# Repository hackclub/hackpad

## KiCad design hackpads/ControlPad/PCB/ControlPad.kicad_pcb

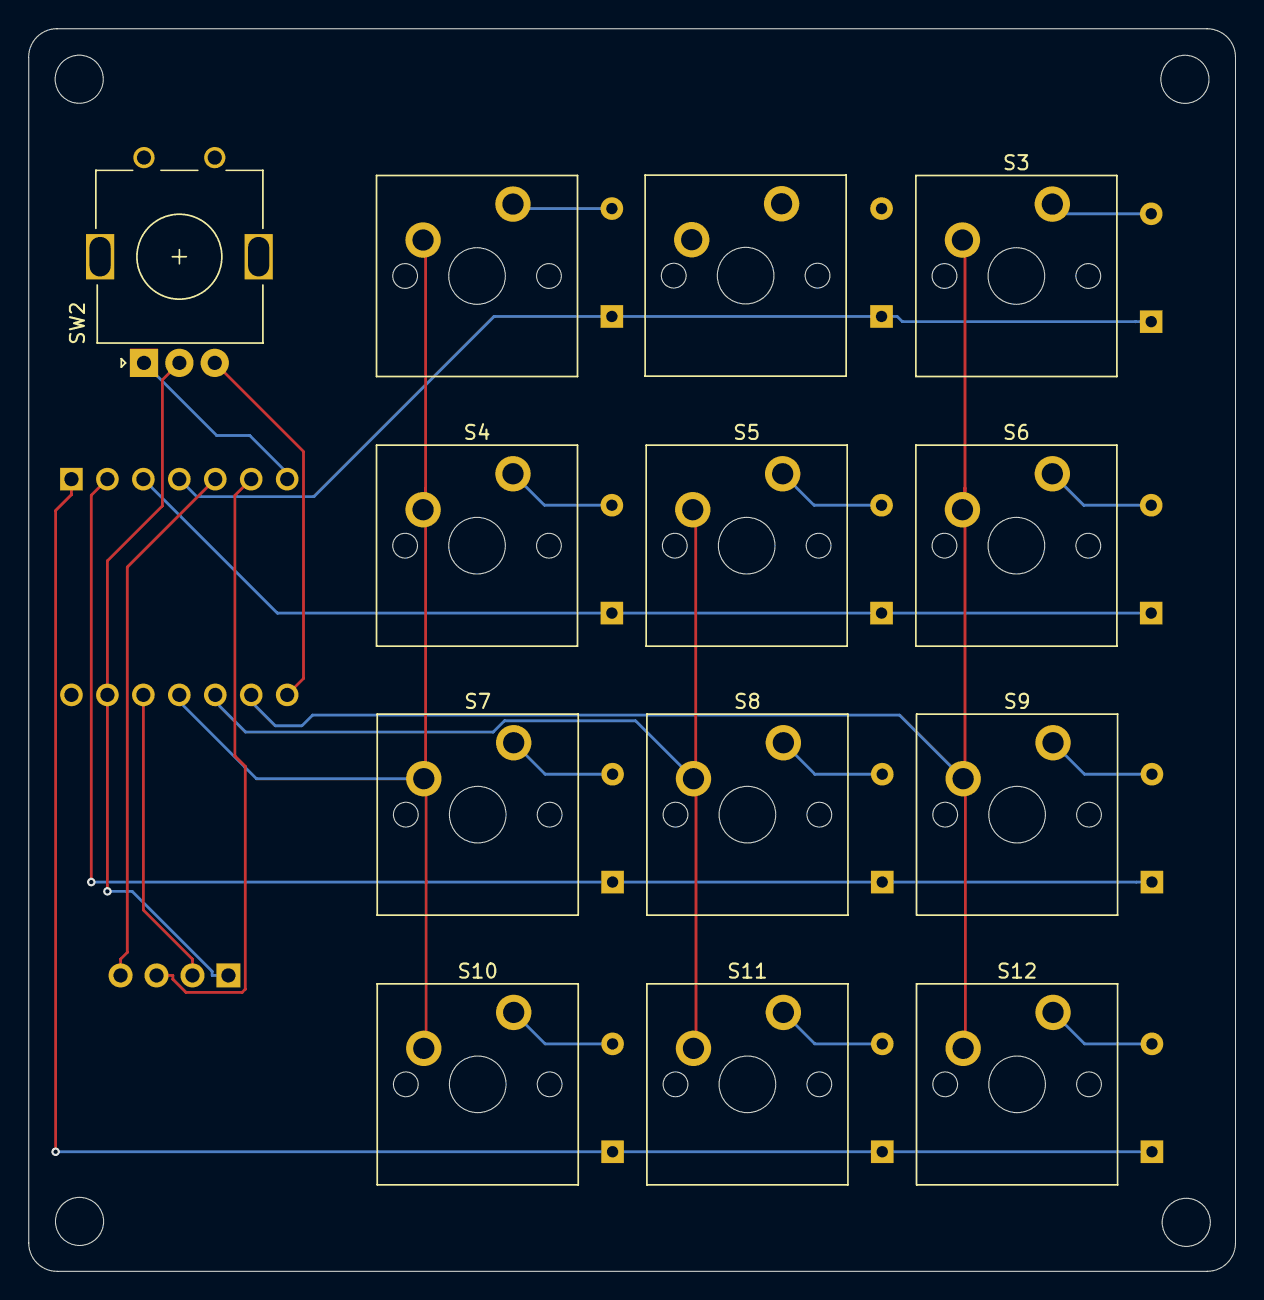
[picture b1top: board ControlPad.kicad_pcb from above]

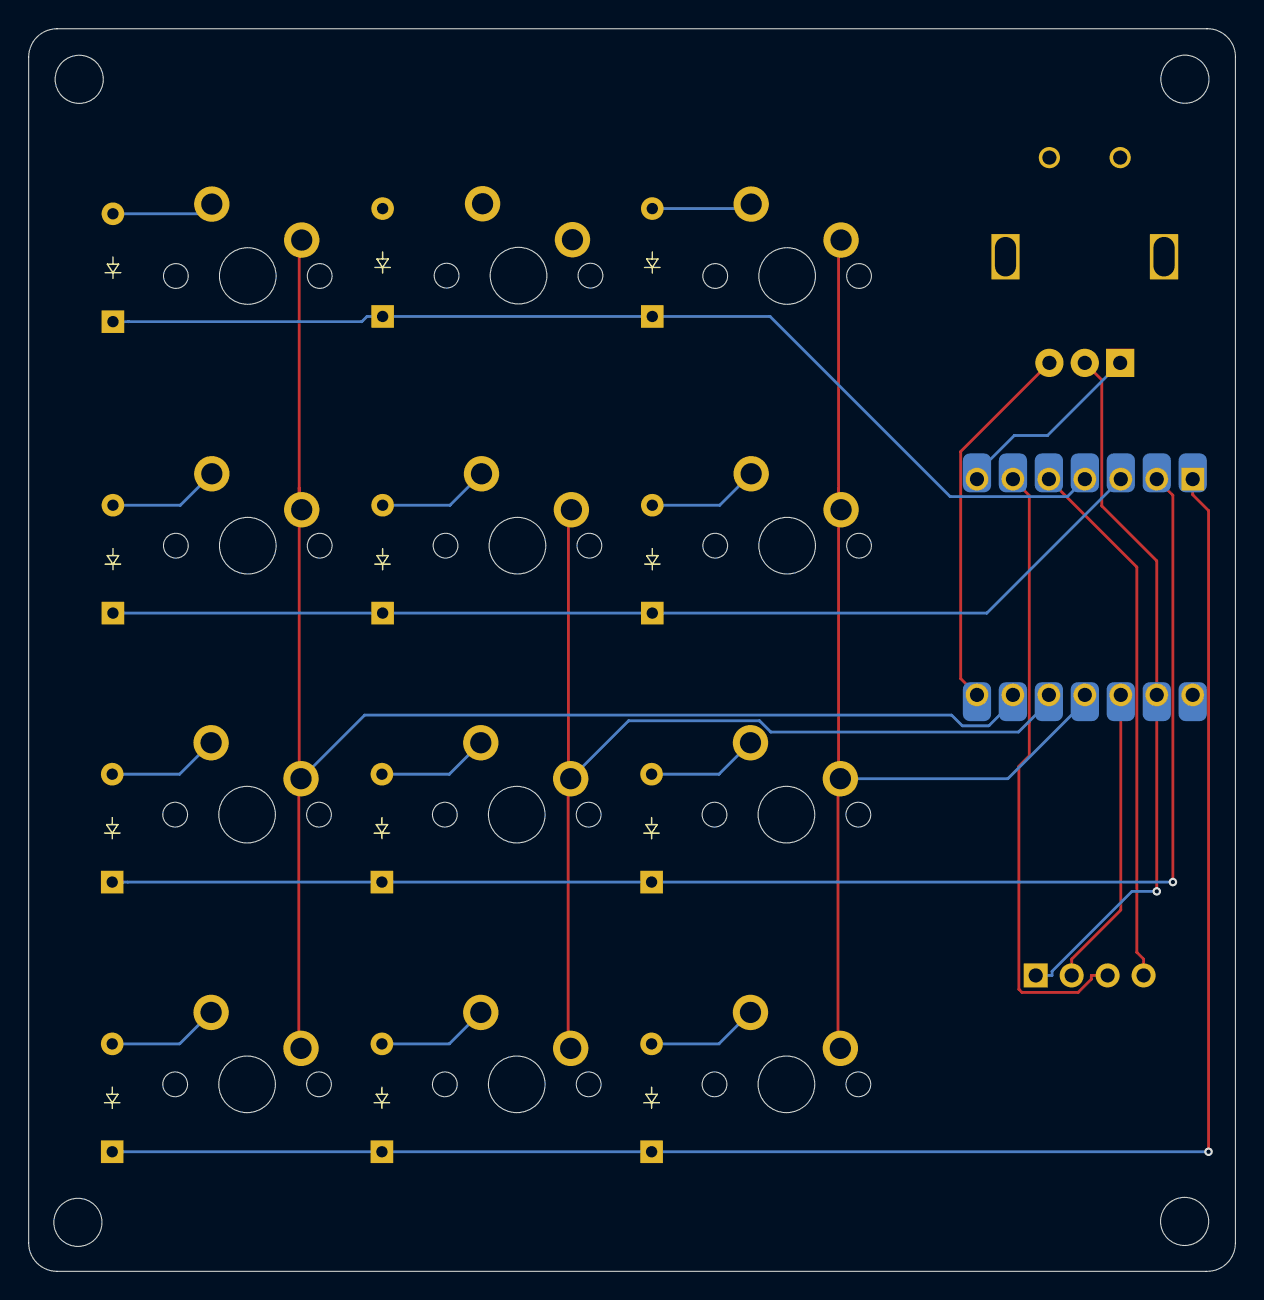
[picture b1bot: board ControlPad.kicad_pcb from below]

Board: 2 copper layers, 85.2 x 87.8 mm, 27 parts (13 on the bottom side), 24 nets.

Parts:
D1, D2, D3, D4, D5, D6, D7, D8, D9, D10, D11, D12: Diode; Diode_DO-35
J2: OLED_128x32
S1, S2, S3, S4, S5, S6, S7, S8, S9, S10, S11, S12: Keyswitch; MX_PCB_1.00u
SW2: RotaryEncoder; RotaryEncoder_Alps_EC11E_Vertical_H20mm
U1: MCU_Seeed_XIAO_RP2040; Seeed_XIAO_RP2040

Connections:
+3.3V: J2.2 (VCC), U1.12 (3V3)
Column 0: S1.1, S4.1, S7.1, S10.1, U1.11 (PA6_A10_D10_MOSI)
Column 1: S5.1, S8.1, S11.1, U1.10 (PA5_A9_D9_MISO)
Column 2: S3.1, S6.1, S9.1, S12.1, U1.9 (PA7_A8_D8_SCK)
GND: J2.1 (GND), SW2.C, U1.13 (GND)
unnamed: D1.2 (A), S1.2
unnamed: D3.2 (A), S3.2
unnamed: D4.2 (A), S4.2
unnamed: D5.2 (A), S5.2
unnamed: D6.2 (A), S6.2
unnamed: D7.2 (A), S7.2
unnamed: D8.2 (A), S8.2
unnamed: D9.2 (A), S9.2
unnamed: D10.2 (A), S10.2
unnamed: D11.2 (A), S11.2
unnamed: D12.2 (A), S12.2
unnamed: J2.3 (SCL), U1.6 (PA9_A5_D5_SCL)
unnamed: J2.4 (SDA), U1.5 (PA8_A4_D4_SDA)
unnamed: SW2.A, U1.7 (PB08_A6_D6_TX)
unnamed: SW2.B, U1.8 (PB09_A7_D7_RX)
Row 0: D1.1 (K), D2.1 (K), D3.1 (K), U1.4 (PA11_A3_D3)
Row 1: D4.1 (K), D5.1 (K), D6.1 (K), U1.3 (PA10_A2_D2)
Row 2: D7.1 (K), D8.1 (K), D9.1 (K), U1.2 (PA4_A1_D1)
Row 3: D10.1 (K), D11.1 (K), D12.1 (K), U1.1 (PA02_A0_D0)

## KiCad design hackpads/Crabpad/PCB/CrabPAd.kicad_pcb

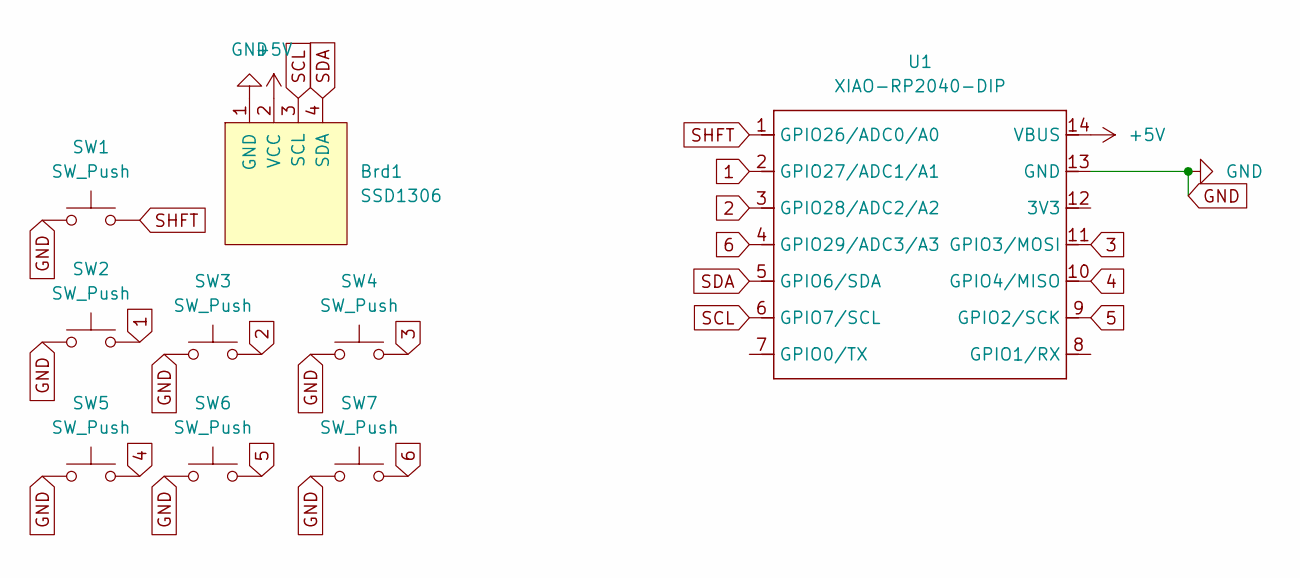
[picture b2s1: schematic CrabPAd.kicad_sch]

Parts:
Brd1: SSD1306; 128x64OLED
SW1, SW2, SW3, SW4, SW5, SW6, SW7: SW_Push; SW_Cherry_MX_1.00u_PCB
U1: XIAO-RP2040-DIP; MCU_Seeed_ESP32C3

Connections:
1: SW2.2, U1.2 (GPIO27/ADC1/A1)
2: SW3.2, U1.3 (GPIO28/ADC2/A2)
3: SW4.2, U1.11 (GPIO3/MOSI)
4: SW5.2, U1.10 (GPIO4/MISO)
5: SW6.2, U1.9 (GPIO2/SCK)
6: SW7.2, U1.4 (GPIO29/ADC3/A3)
+5V: Brd1.2 (VCC), U1.14 (VBUS)
GND: Brd1.1 (GND), SW1.1, SW2.1, SW3.1, SW4.1, SW5.1, SW6.1, SW7.1, U1.13 (GND)
SCL: Brd1.3 (SCL), U1.6 (GPIO7/SCL)
SDA: Brd1.4 (SDA), U1.5 (GPIO6/SDA)
SHFT: SW1.2, U1.1 (GPIO26/ADC0/A0)

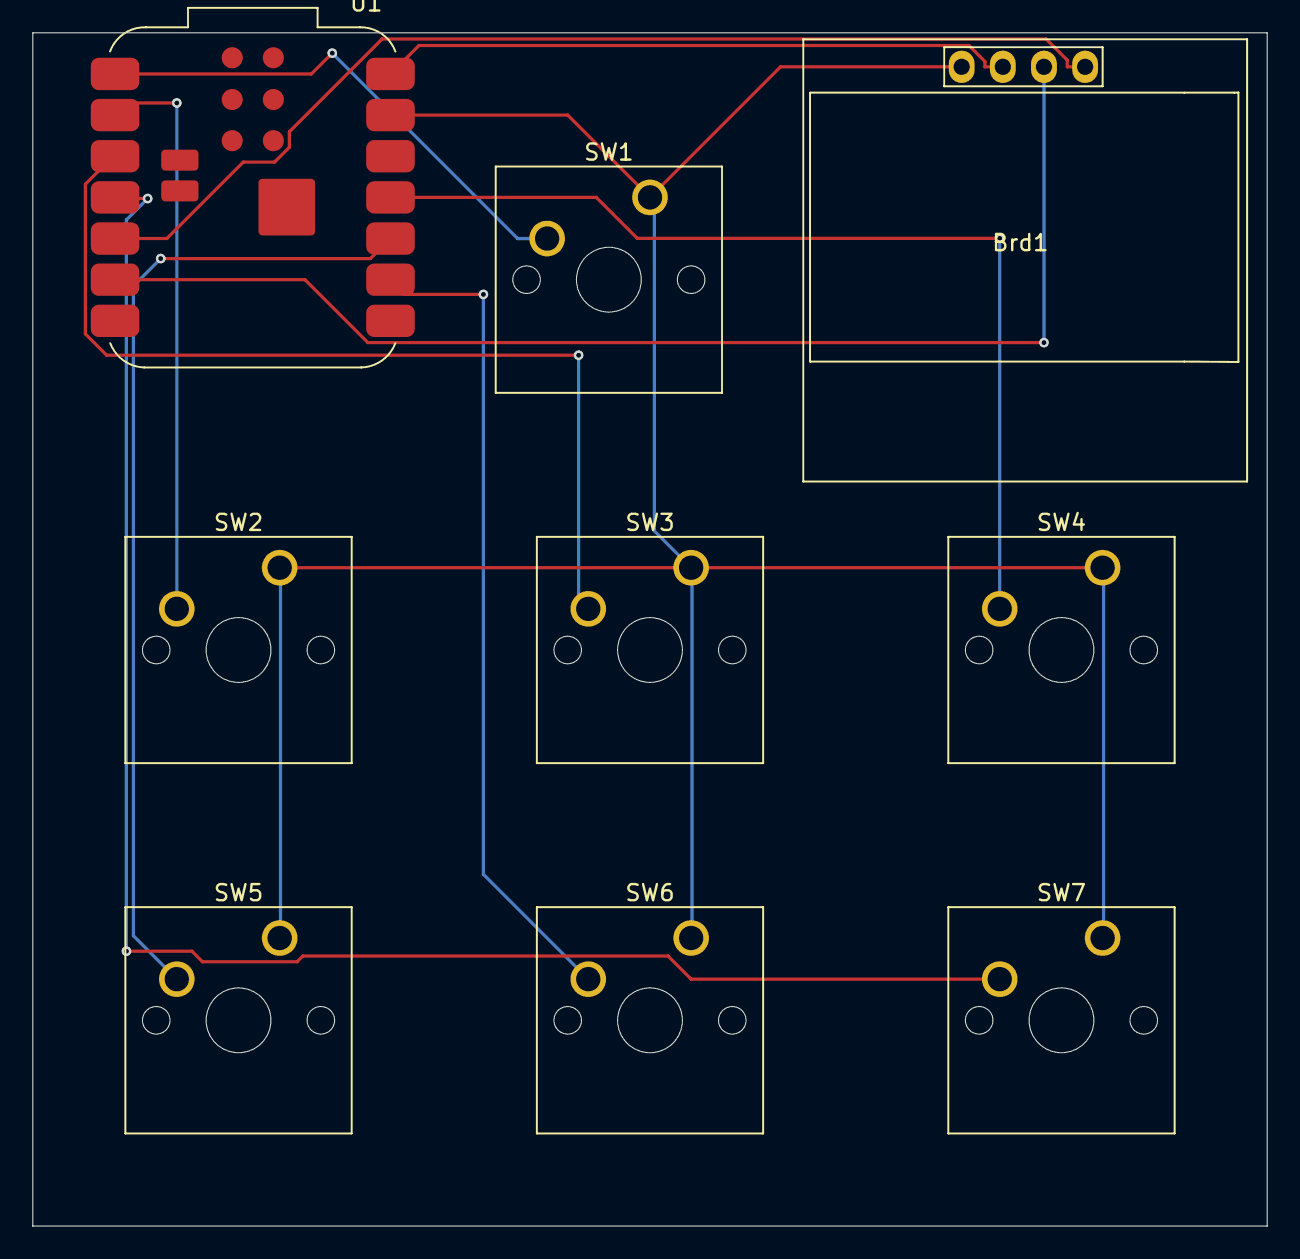
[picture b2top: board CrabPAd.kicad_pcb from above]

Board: 2 copper layers, 76.2 x 73.7 mm, 9 parts (0 on the bottom side), 11 nets.

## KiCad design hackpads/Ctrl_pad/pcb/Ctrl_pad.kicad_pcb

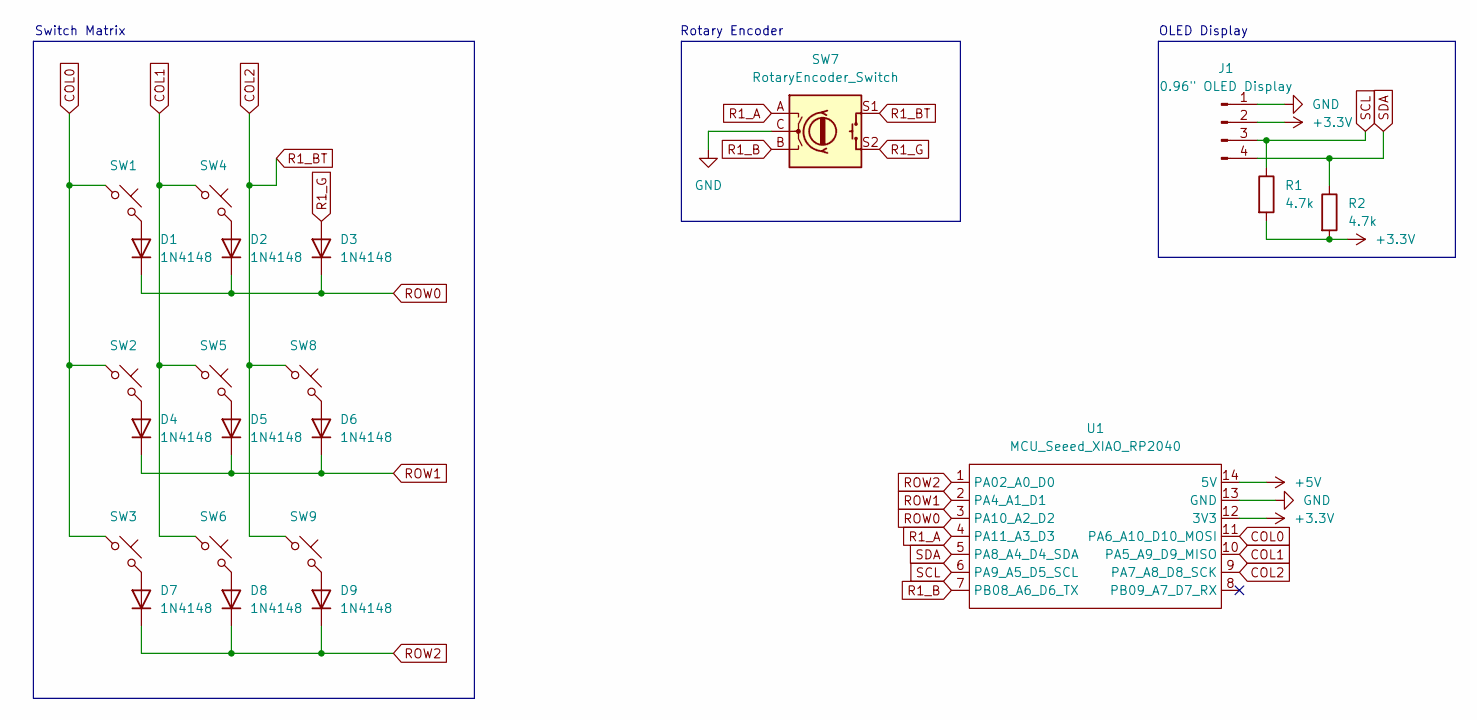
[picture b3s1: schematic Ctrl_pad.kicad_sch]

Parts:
D1, D2, D3, D4, D5, D6, D7, D8, D9: 1N4148; D_DO-35_SOD27_P7.62mm_Horizontal
J1: 0.96" OLED Display; OLED_128x64
R1, R2: 4.7k; R_Axial_DIN0204_L3.6mm_D1.6mm_P5.08mm_Horizontal
SW1, SW2, SW3, SW4, SW5, SW6, SW8, SW9: MX; MX_PCB_1.00u
SW7: RotaryEncoder_Switch; Encoder_EC11_MX
U1: MCU_Seeed_XIAO_RP2040; Seeed_XIAO_RP2040

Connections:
+3.3V: J1.2, R1.2, R2.2, U1.12 (3V3)
+5V: U1.14 (5V)
COL0: SW1.1, SW2.1, SW3.1, U1.11 (PA6_A10_D10_MOSI)
COL1: SW4.1, SW5.1, SW6.1, U1.10 (PA5_A9_D9_MISO)
COL2: SW7.S1, SW8.1, SW9.1, U1.9 (PA7_A8_D8_SCK)
GND: J1.1, SW7.C, U1.13 (GND)
unnamed: D1.2 (A), SW1.2
unnamed: D2.2 (A), SW4.2
unnamed: D4.2 (A), SW2.2
unnamed: D5.2 (A), SW5.2
unnamed: D6.2 (A), SW8.2
unnamed: D7.2 (A), SW3.2
unnamed: D8.2 (A), SW6.2
unnamed: D9.2 (A), SW9.2
R1_A: SW7.A, U1.4 (PA11_A3_D3)
R1_B: SW7.B, U1.7 (PB08_A6_D6_TX)
R1_G: D3.2 (A), SW7.S2
ROW0: D1.1 (K), D2.1 (K), D3.1 (K), U1.3 (PA10_A2_D2)
ROW1: D4.1 (K), D5.1 (K), D6.1 (K), U1.2 (PA4_A1_D1)
ROW2: D7.1 (K), D8.1 (K), D9.1 (K), U1.1 (PA02_A0_D0)
SCL: J1.3, R1.1, U1.6 (PA9_A5_D5_SCL)
SDA: J1.4, R2.1, U1.5 (PA8_A4_D4_SDA)

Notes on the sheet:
Rotary Encoder
OLED Display
Switch Matrix

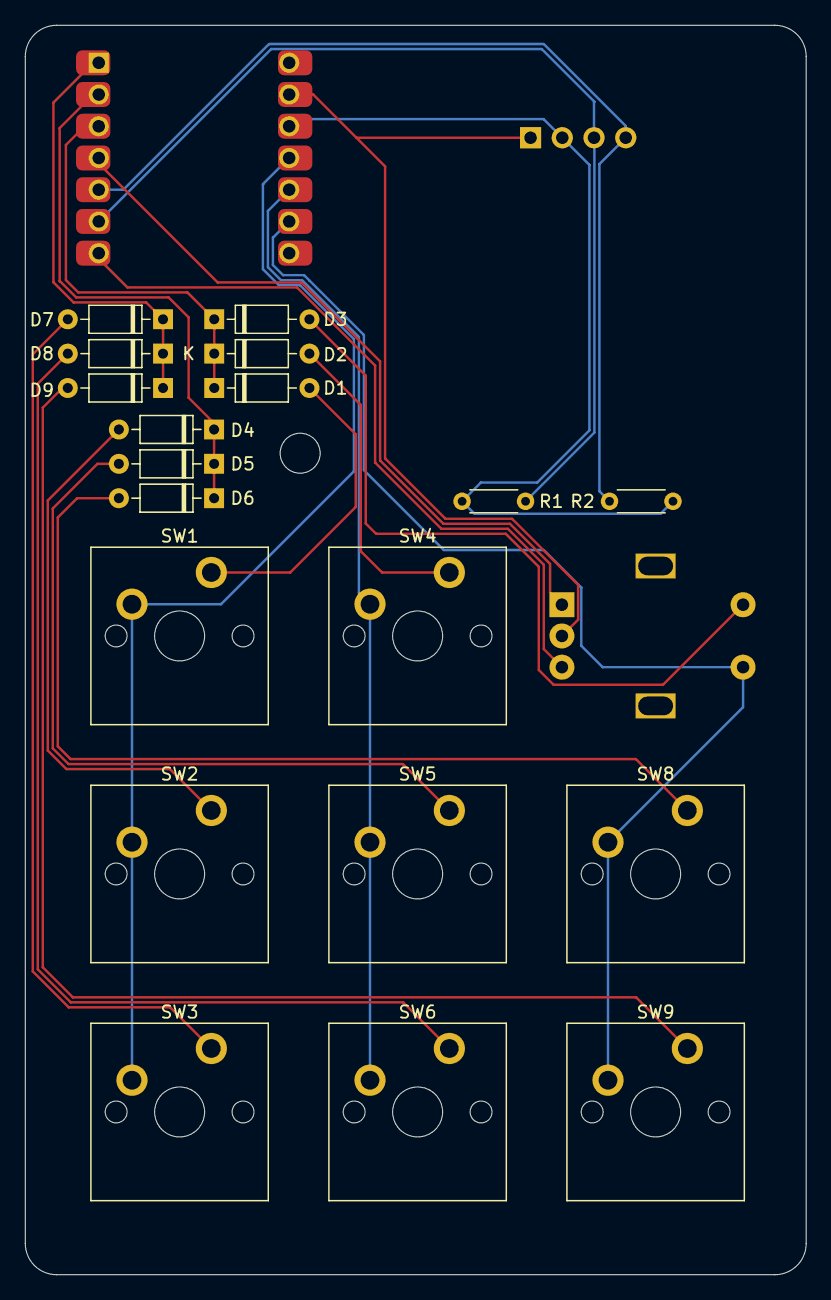
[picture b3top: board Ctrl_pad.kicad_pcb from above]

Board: 2 copper layers, 62.5 x 100.0 mm, 22 parts (0 on the bottom side), 21 nets.

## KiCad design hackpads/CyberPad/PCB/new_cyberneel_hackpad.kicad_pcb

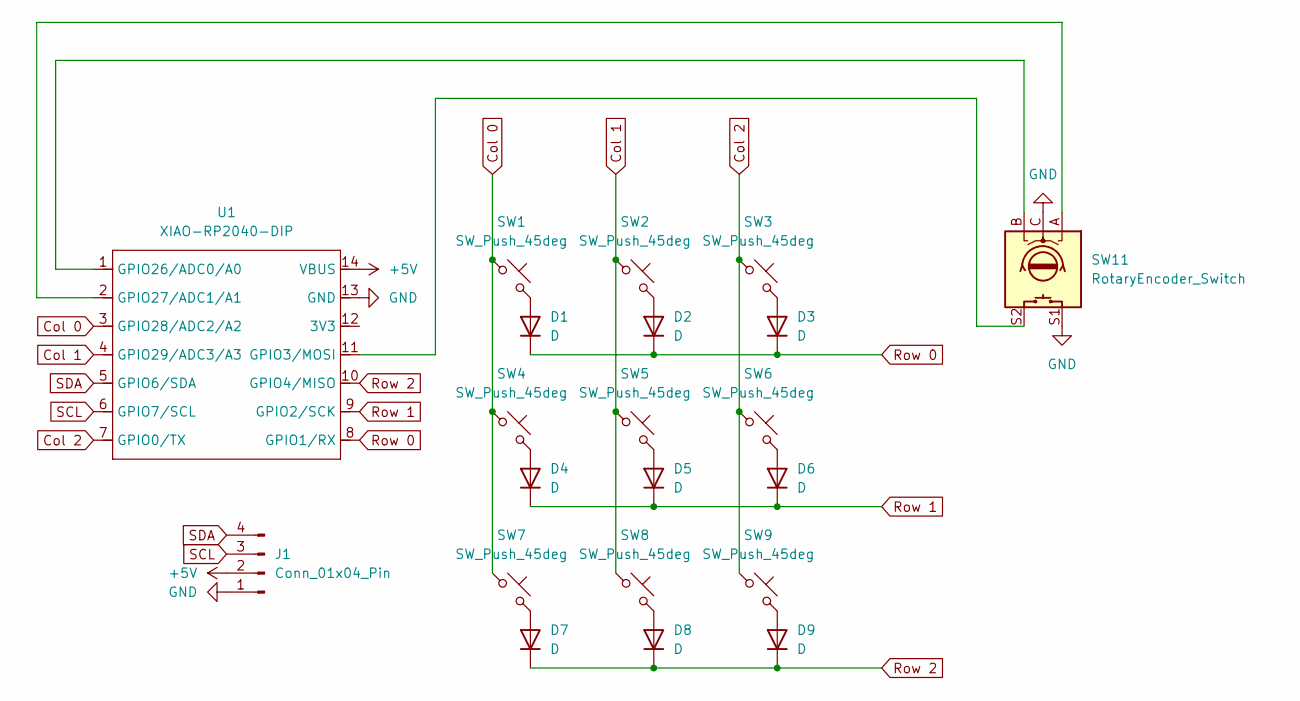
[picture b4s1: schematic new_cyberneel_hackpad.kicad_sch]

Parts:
D1, D2, D3, D4, D5, D6, D7, D8, D9: D; D_DO-35_SOD27_P7.62mm_Horizontal
J1: Conn_01x04_Pin; OLED_128x64
SW1, SW2, SW3, SW4, SW5, SW6, SW7, SW8, SW9: SW_Push_45deg; MX_PCB_1.00u
SW11: RotaryEncoder_Switch; RotaryEncoder_Alps_EC11E-Switch_Vertical_H20mm_MountingHoles
U1: XIAO-RP2040-DIP

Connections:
+5V: J1.2, U1.14 (VBUS)
Col 0: SW1.1, SW4.1, SW7.1, U1.3 (GPIO28/ADC2/A2)
Col 1: SW2.1, SW5.1, SW8.1, U1.4 (GPIO29/ADC3/A3)
Col 2: SW3.1, SW6.1, SW9.1, U1.7 (GPIO0/TX)
GND: J1.1, SW11.C, SW11.S1, U1.13 (GND)
unnamed: D1.2 (A), SW1.2
unnamed: D2.2 (A), SW2.2
unnamed: D3.2 (A), SW3.2
unnamed: D4.2 (A), SW4.2
unnamed: D5.2 (A), SW5.2
unnamed: D6.2 (A), SW6.2
unnamed: D7.2 (A), SW7.2
unnamed: D8.2 (A), SW8.2
unnamed: D9.2 (A), SW9.2
unnamed: SW11.S2, U1.11 (GPIO3/MOSI)
unnamed: SW11.B, U1.1 (GPIO26/ADC0/A0)
unnamed: SW11.A, U1.2 (GPIO27/ADC1/A1)
Row 0: D1.1 (K), D2.1 (K), D3.1 (K), U1.8 (GPIO1/RX)
Row 1: D4.1 (K), D5.1 (K), D6.1 (K), U1.9 (GPIO2/SCK)
Row 2: D7.1 (K), D8.1 (K), D9.1 (K), U1.10 (GPIO4/MISO)
SCL: J1.3, U1.6 (GPIO7/SCL)
SDA: J1.4, U1.5 (GPIO6/SDA)

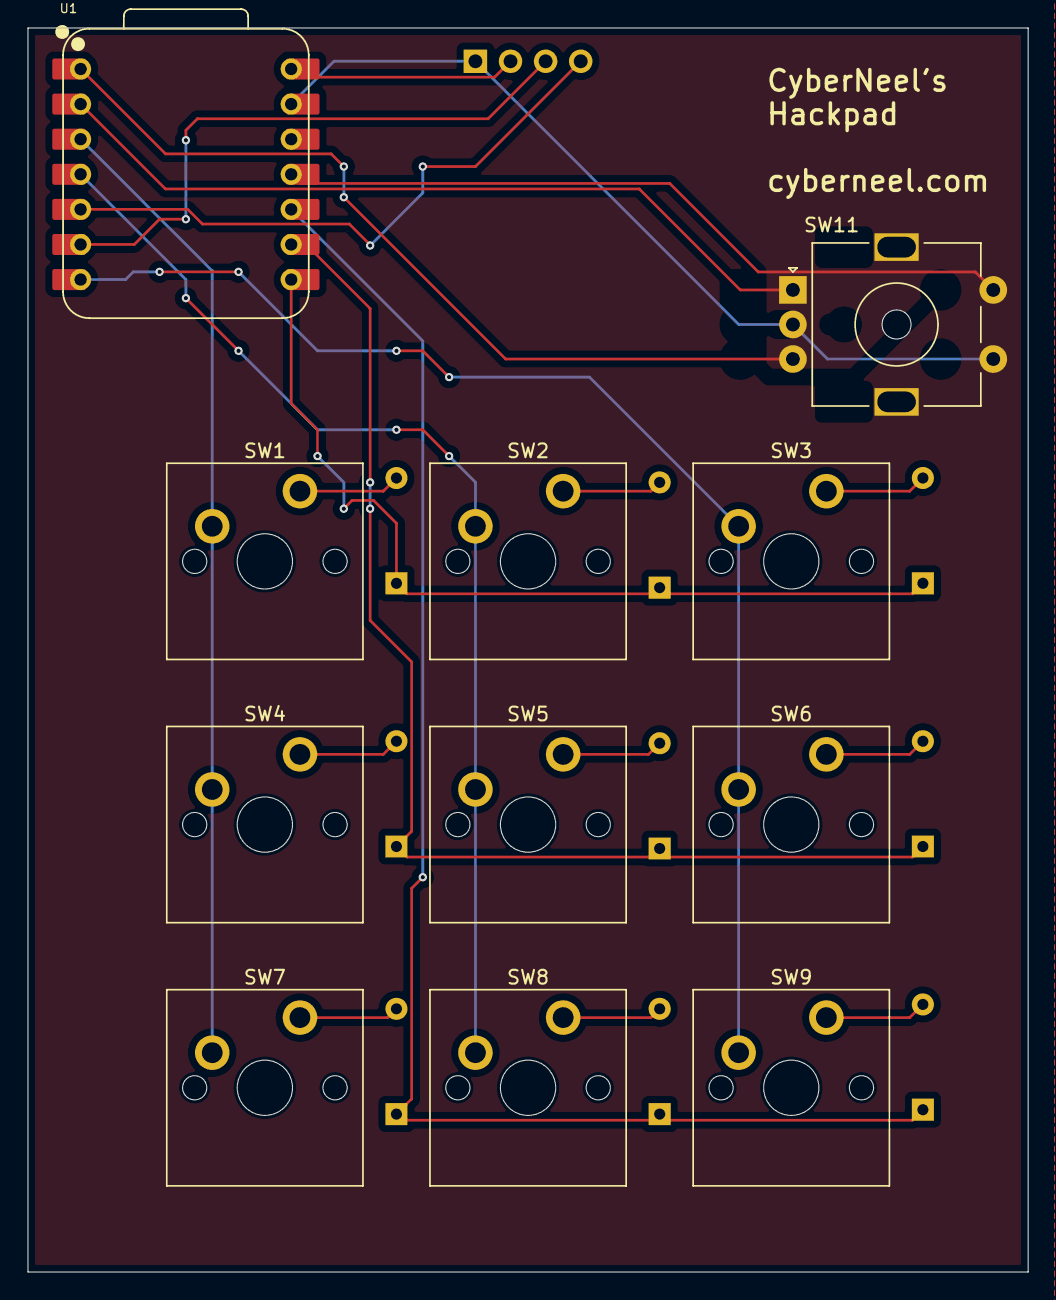
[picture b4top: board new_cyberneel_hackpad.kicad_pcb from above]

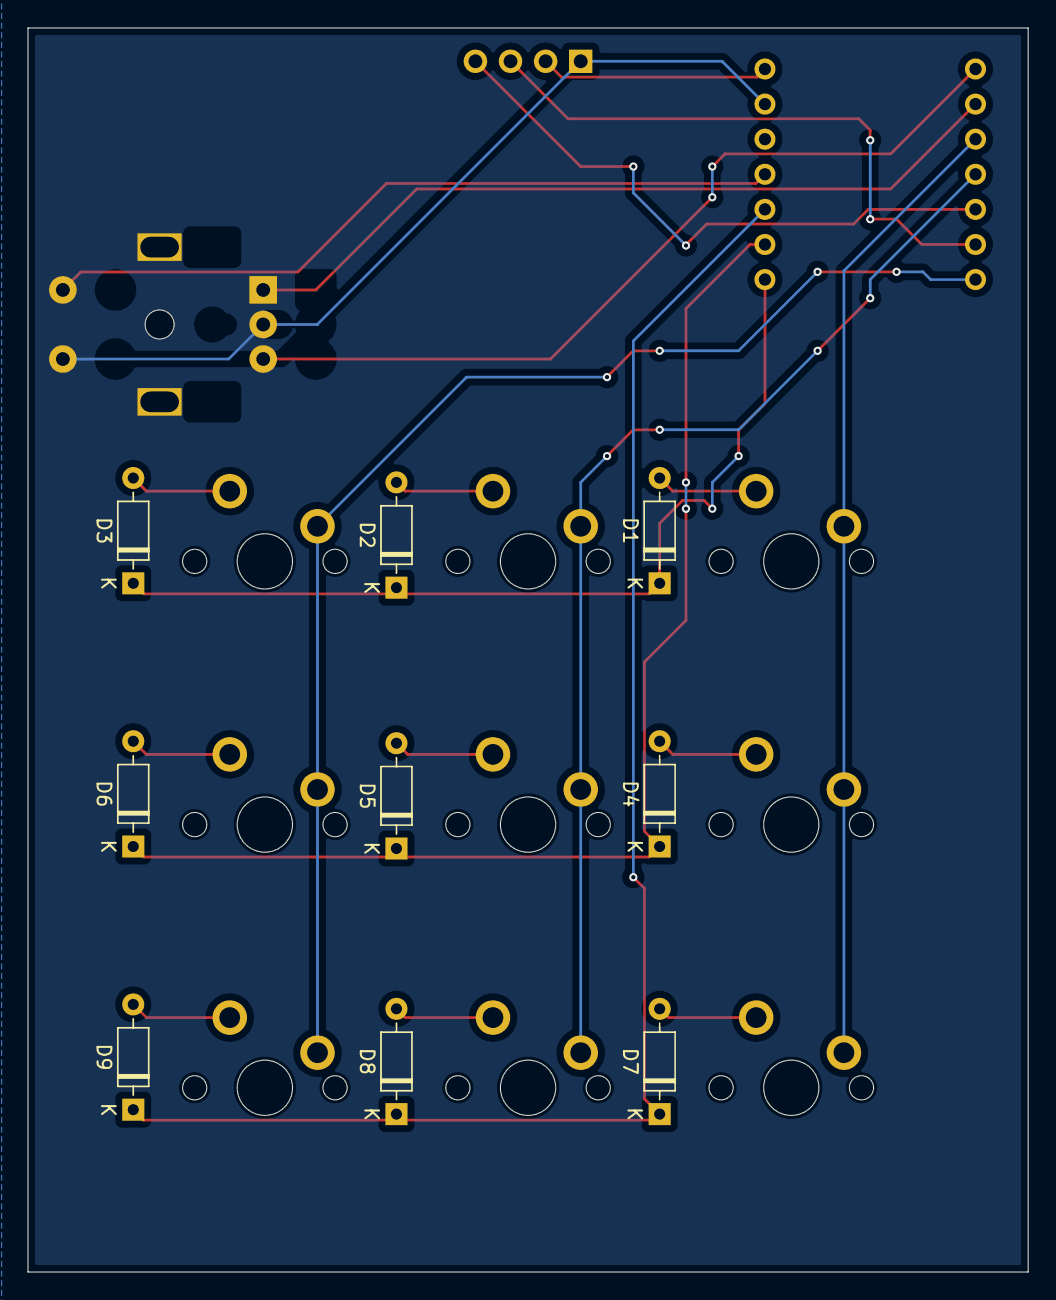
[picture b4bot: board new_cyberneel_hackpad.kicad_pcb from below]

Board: 2 copper layers, 72.4 x 90.0 mm, 21 parts (9 on the bottom side), 22 nets.

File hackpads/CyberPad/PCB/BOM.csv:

"Reference","Value","Datasheet","Footprint","Qty","DNP"
"D1,D2,D3,D4,D5,D6,D7,D8,D9","D","~","Diode_THT:D_DO-35_SOD27_P7.62mm_Horizontal","9",""
"J1","Conn_01x04_Pin","~","ScottoKeebs_Components:OLED_128x64","1",""
"SW1,SW2,SW3,SW4,SW5,SW6,SW7,SW8,SW9","SW_Push_45deg","~","ScottoKeebs_MX:MX_PCB_1.00u","9",""
"SW11","RotaryEncoder_Switch","~","Rotary_Encoder:RotaryEncoder_Alps_EC11E-Switch_Vertical_H20mm_MountingHoles","1",""
"U1","XIAO-RP2040-DIP","","OPL:XIAO-RP2040-DIP","1",""

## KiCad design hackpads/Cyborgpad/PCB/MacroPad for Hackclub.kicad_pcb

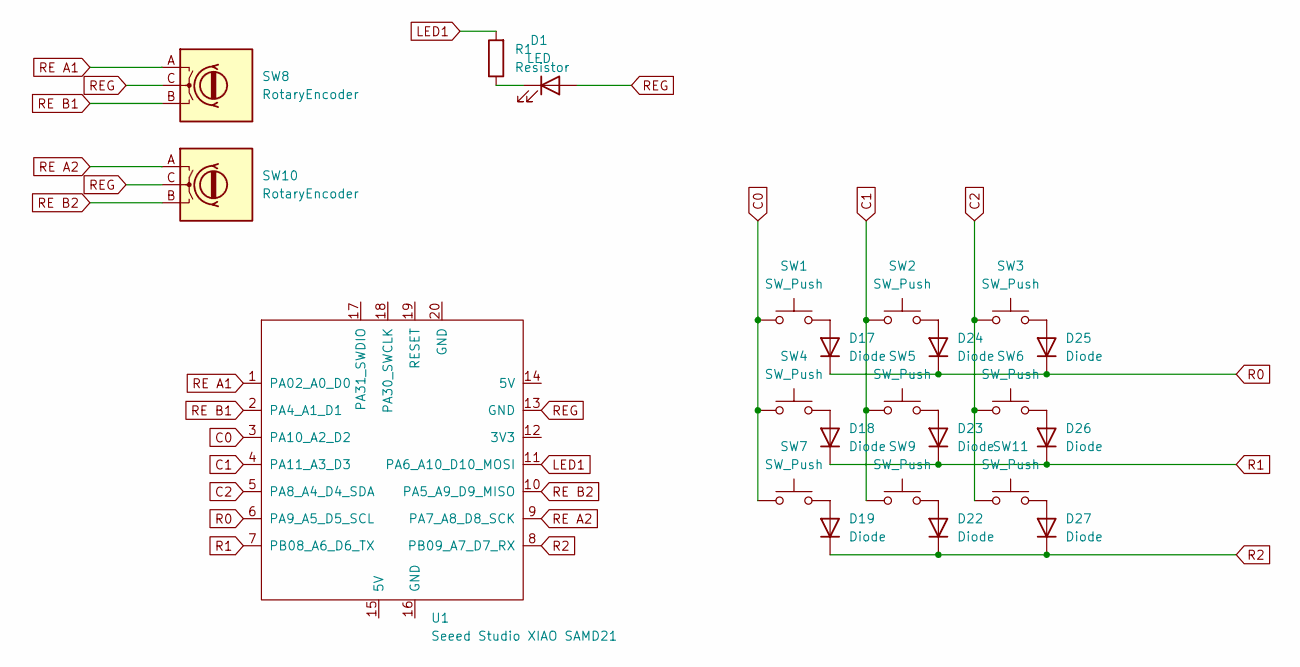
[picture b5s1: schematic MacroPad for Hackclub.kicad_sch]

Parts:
D1: LED; LED_D1.8mm_W1.8mm_H2.4mm_Horizontal_O1.27mm_Z8.2mm
D17, D18, D19, D22, D23, D24, D25, D26, D27: Diode; D_DO-35_SOD27_P12.70mm_Horizontal
R1: Resistor; R_Axial_DIN0207_L6.3mm_D2.5mm_P7.62mm_Horizontal
SW1, SW2, SW3, SW4, SW5, SW6, SW7, SW9, SW11: SW_Push; SW_Cherry_MX_1.00u_PCB
SW8, SW10: RotaryEncoder; RotaryEncoder_Alps_EC11E_Vertical_H20mm
U1: Seeed Studio XIAO SAMD21; XIAO-Generic-Thruhole-14P-2.54-21X17.8MM

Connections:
C0: SW1.1, SW4.1, SW7.1, U1.3 (PA10_A2_D2)
C1: SW2.1, SW5.1, SW9.1, U1.4 (PA11_A3_D3)
C2: SW3.1, SW6.1, SW11.1, U1.5 (PA8_A4_D4_SDA)
LED1: R1.2, U1.11 (PA6_A10_D10_MOSI)
unnamed: D1.1 (K), R1.1
unnamed: D17.2 (A), SW1.2
unnamed: D18.2 (A), SW4.2
unnamed: D19.2 (A), SW7.2
unnamed: D22.2 (A), SW9.2
unnamed: D23.2 (A), SW5.2
unnamed: D24.2 (A), SW2.2
unnamed: D25.2 (A), SW3.2
unnamed: D26.2 (A), SW6.2
unnamed: D27.2 (A), SW11.2
R0: D17.1 (K), D24.1 (K), D25.1 (K), U1.6 (PA9_A5_D5_SCL)
R1: D18.1 (K), D23.1 (K), D26.1 (K), U1.7 (PB08_A6_D6_TX)
R2: D19.1 (K), D22.1 (K), D27.1 (K), U1.8 (PB09_A7_D7_RX)
RE A1: SW8.A, U1.1 (PA02_A0_D0)
RE A2: SW10.A, U1.9 (PA7_A8_D8_SCK)
RE B1: SW8.B, U1.2 (PA4_A1_D1)
RE B2: SW10.B, U1.10 (PA5_A9_D9_MISO)
REG: D1.2 (A), SW8.C, SW10.C, U1.13 (GND)

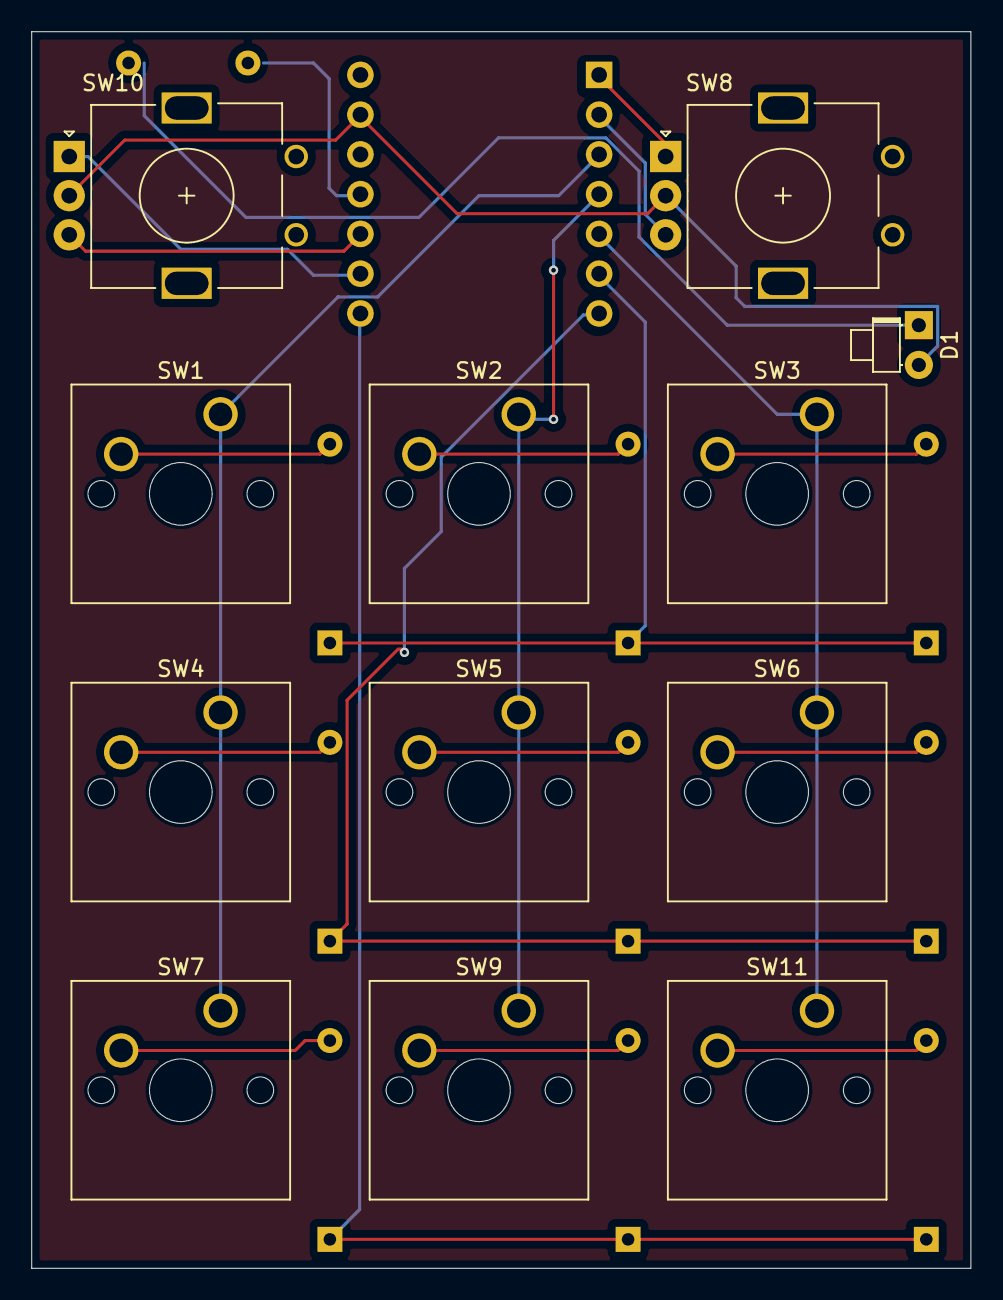
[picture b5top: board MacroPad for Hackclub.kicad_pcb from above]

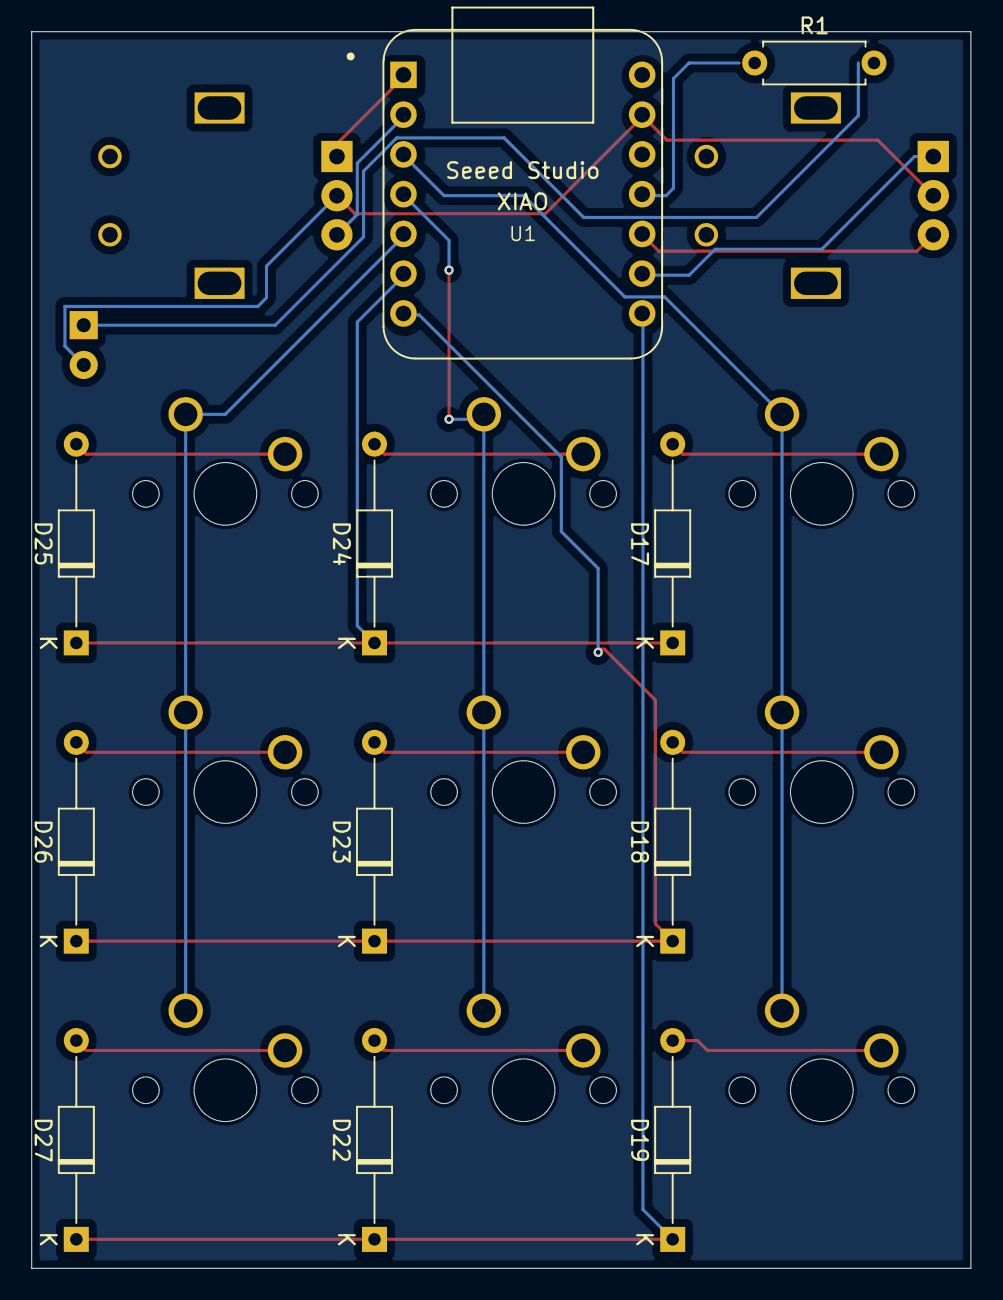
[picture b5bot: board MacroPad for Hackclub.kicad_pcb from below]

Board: 2 copper layers, 60.0 x 79.0 mm, 23 parts (11 on the bottom side), 22 nets.

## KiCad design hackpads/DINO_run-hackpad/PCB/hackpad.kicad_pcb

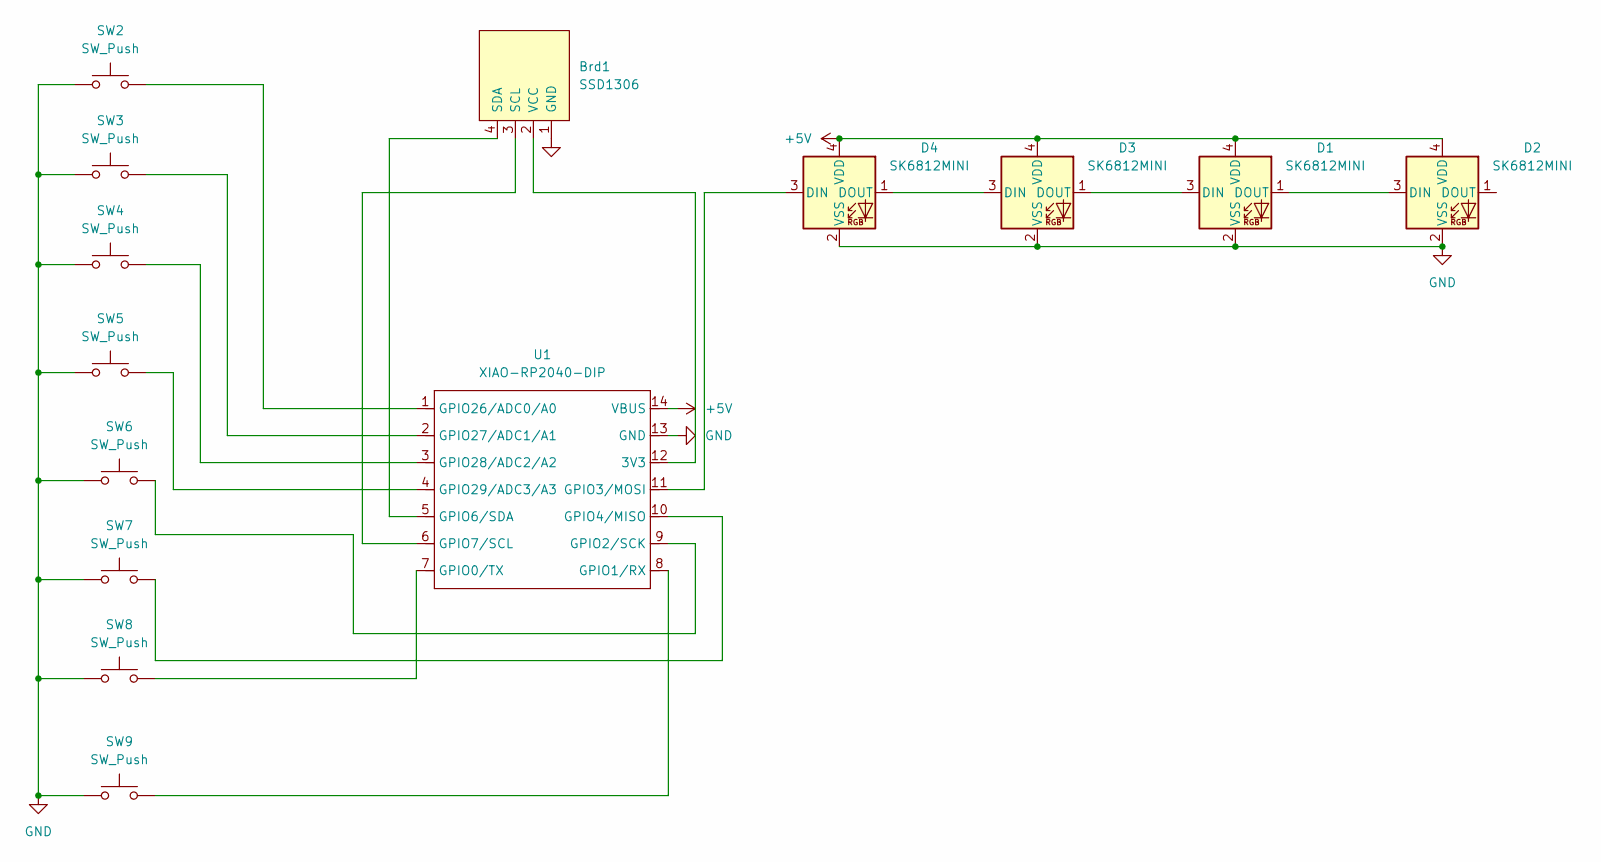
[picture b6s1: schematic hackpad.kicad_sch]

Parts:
Brd1: SSD1306; Adafruit_SSD1306
D1, D2, D3, D4: SK6812MINI; LED_SK6812MINI_PLCC4_3.5x3.5mm_P1.75mm
SW2, SW3, SW4, SW5, SW6, SW7, SW8, SW9: SW_Push; SW_Cherry_MX_1.00u_PCB
U1: XIAO-RP2040-DIP

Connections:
+5V: D1.4 (VDD), D2.4 (VDD), D3.4 (VDD), D4.4 (VDD), U1.14 (VBUS)
GND: D1.2 (VSS), D2.2 (VSS), D3.2 (VSS), D4.2 (VSS), SW2.1, SW3.1, SW4.1, SW5.1, SW6.1, SW7.1, SW8.1, SW9.1, U1.13 (GND)
unnamed: Brd1.3 (SCL), U1.6 (GPIO7/SCL)
unnamed: Brd1.4 (SDA), U1.5 (GPIO6/SDA)
unnamed: Brd1.2 (VCC), U1.12 (3V3)
unnamed: D1.3 (DIN), D3.1 (DOUT)
unnamed: D1.1 (DOUT), D2.3 (DIN)
unnamed: D3.3 (DIN), D4.1 (DOUT)
unnamed: D4.3 (DIN), U1.11 (GPIO3/MOSI)
unnamed: SW8.2, U1.7 (GPIO0/TX)
unnamed: SW9.2, U1.8 (GPIO1/RX)
unnamed: SW6.2, U1.9 (GPIO2/SCK)
unnamed: SW7.2, U1.10 (GPIO4/MISO)
unnamed: SW2.2, U1.1 (GPIO26/ADC0/A0)
unnamed: SW3.2, U1.2 (GPIO27/ADC1/A1)
unnamed: SW4.2, U1.3 (GPIO28/ADC2/A2)
unnamed: SW5.2, U1.4 (GPIO29/ADC3/A3)

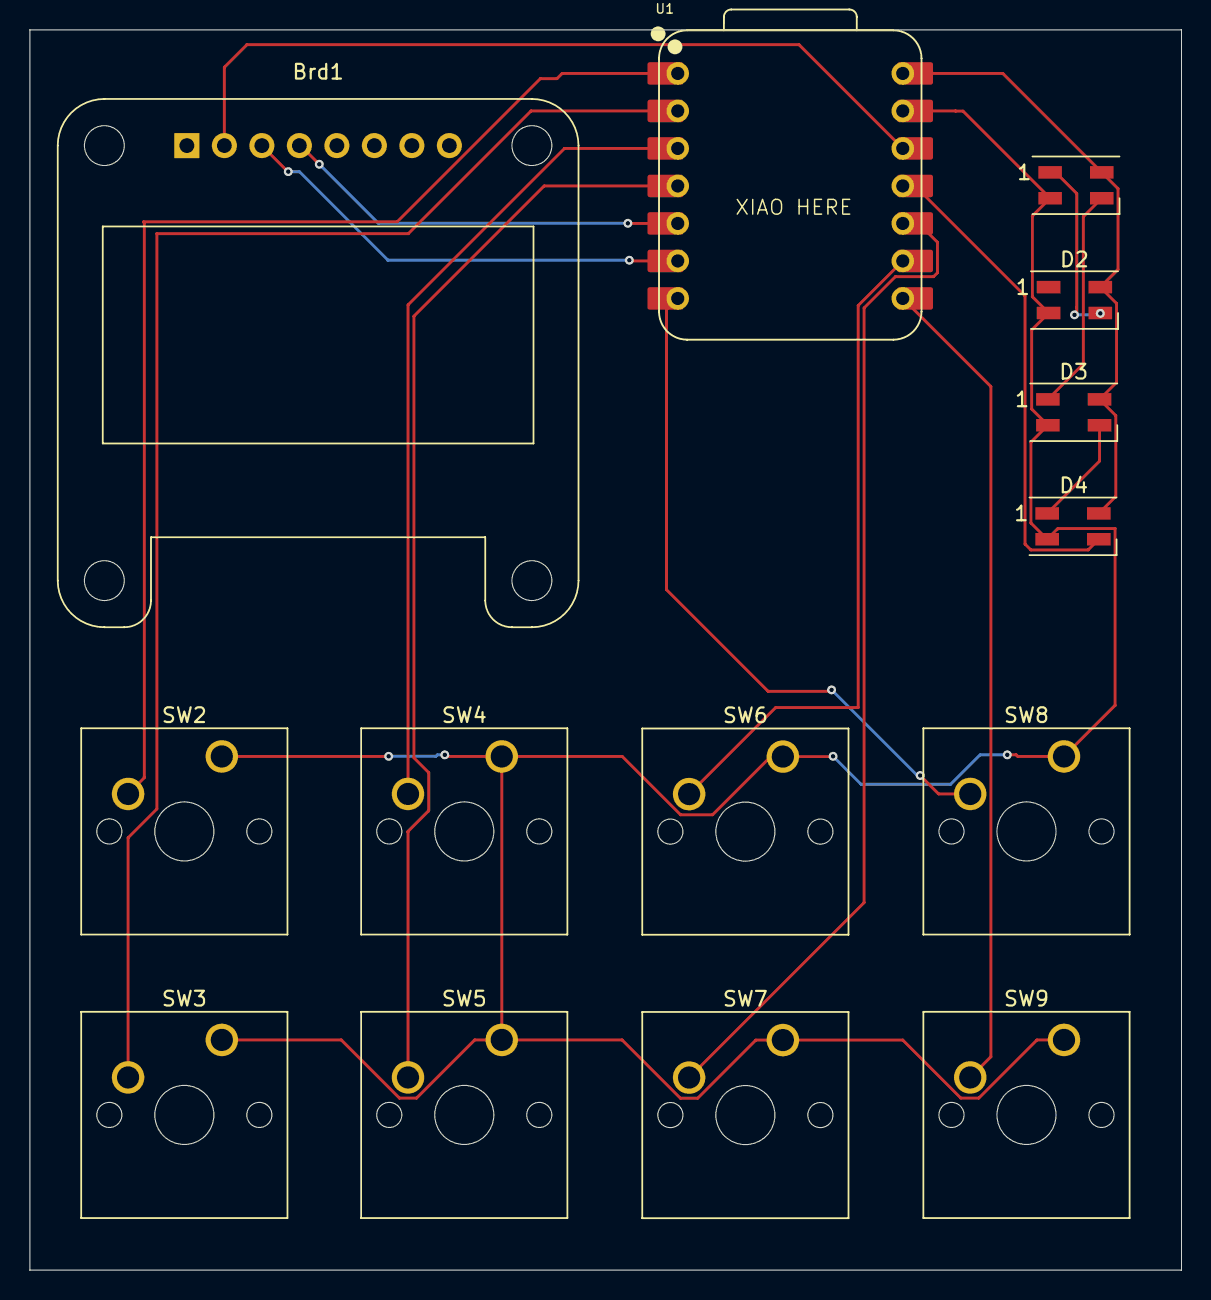
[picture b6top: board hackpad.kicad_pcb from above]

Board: 2 copper layers, 78.0 x 84.0 mm, 14 parts (0 on the bottom side), 17 nets.
